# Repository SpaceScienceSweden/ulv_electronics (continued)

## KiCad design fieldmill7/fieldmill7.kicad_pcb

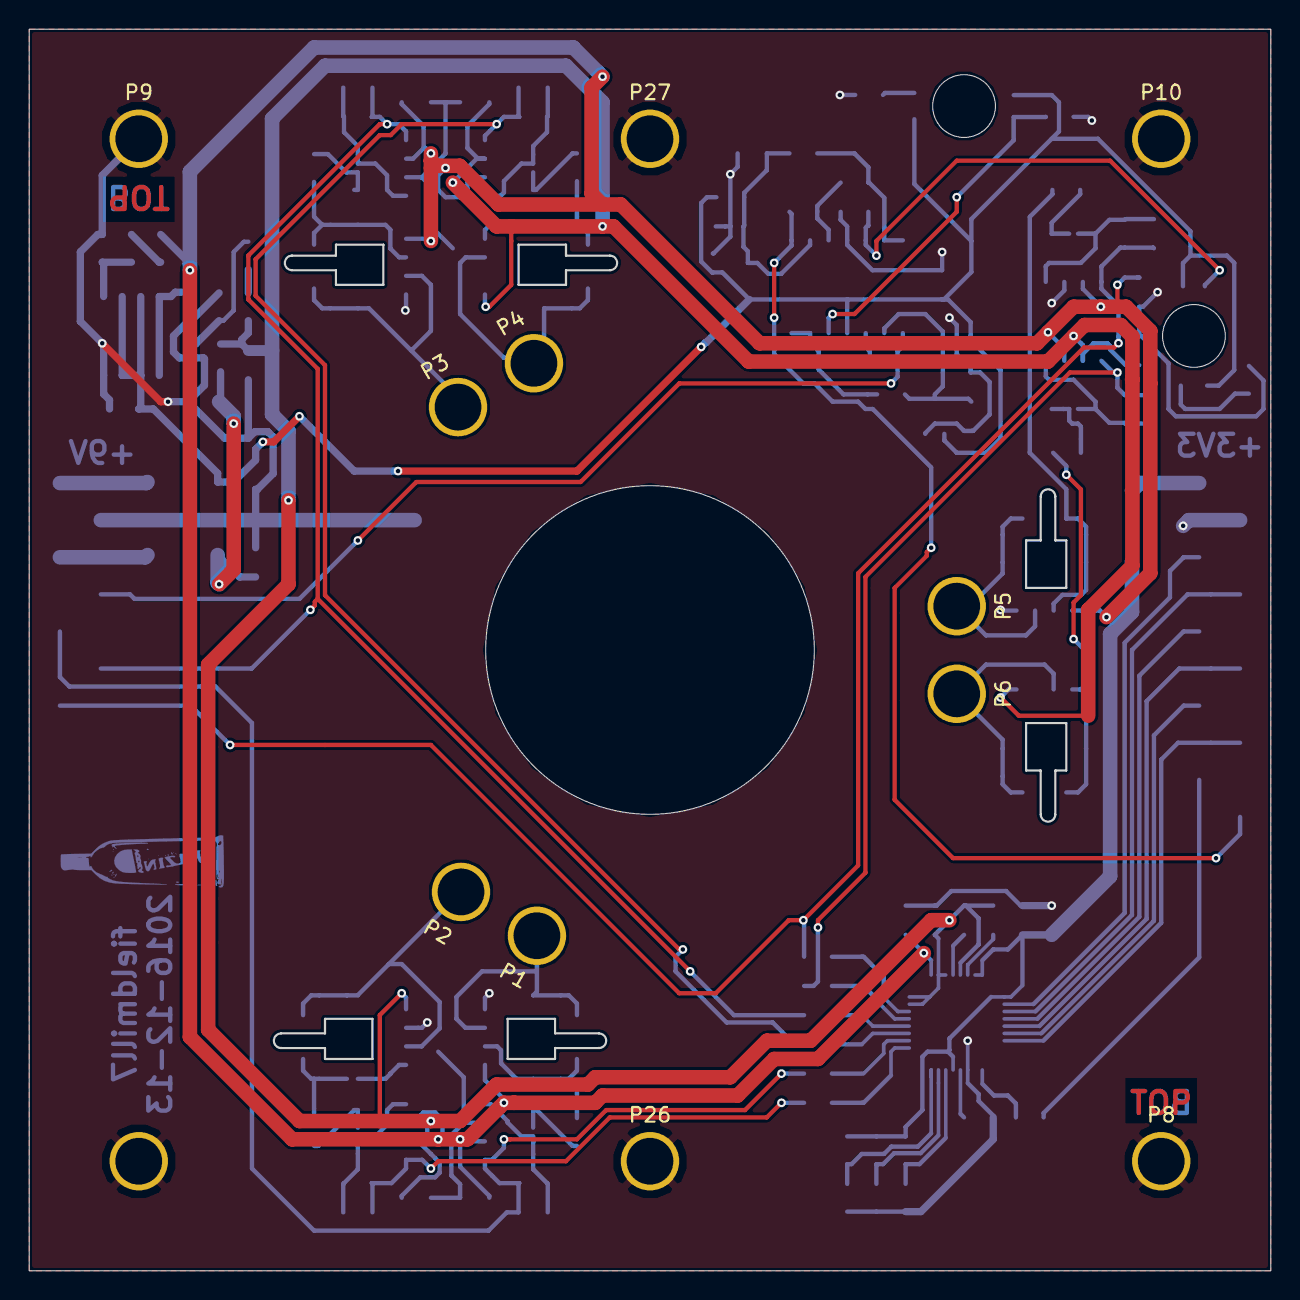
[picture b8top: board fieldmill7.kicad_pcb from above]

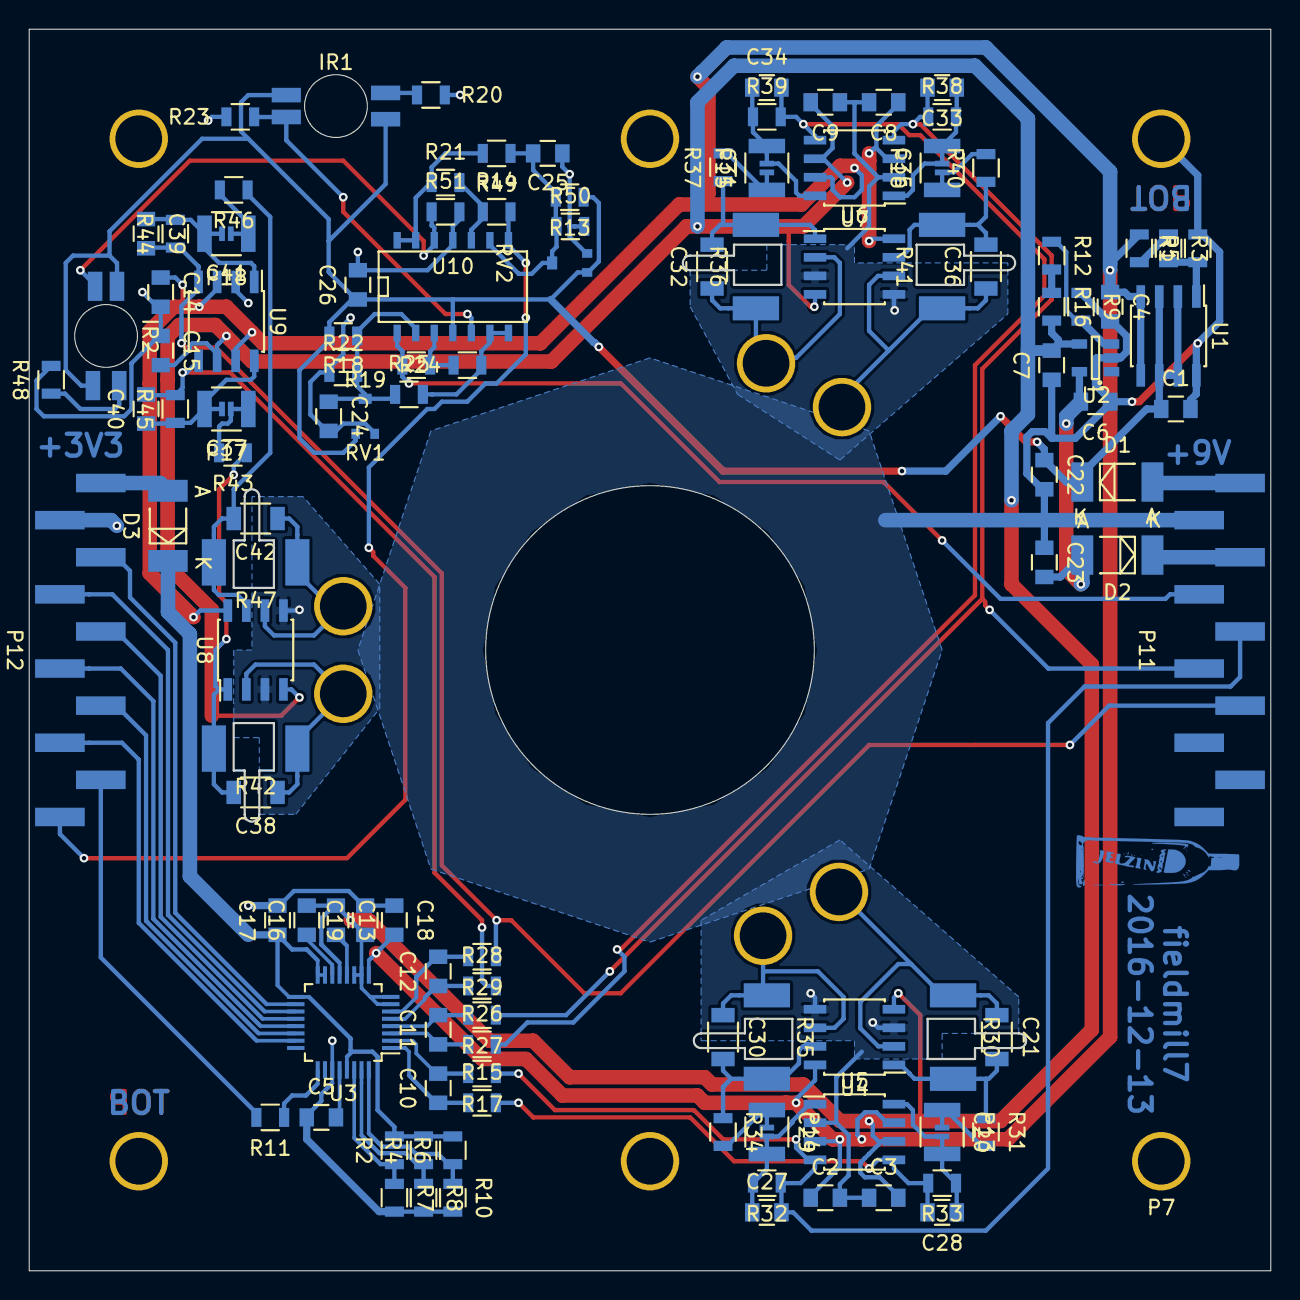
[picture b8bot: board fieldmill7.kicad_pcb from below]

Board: 2 copper layers, 85.0 x 85.0 mm, 130 parts (119 on the bottom side), 75 nets.

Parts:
C1, C2, C3, C6, C8, C9, C14, C15, C24, C25, C26: 100n; C_0805
C4, C7, C22, C23: 10u; C_0805
C5, C13, C16, C17, C18, C19: 1u; C_0805
C10, C11, C12: 10n; C_0805
C20, C29, C31, C35, C37, C41: 220n; C_1210
C21, C30, C32, C36, C38, C42: 10p; C_1206
C27, C28, C33, C34, C39, C40: 1n; C_0805
D1, D2, D3: SMS240; MELF_Standard
IR1, IR2: SG-2BC
P1, P2, P3, P4, P5, P6: SENSOR; M3_PTH
P7, P8, P9, P10, P26, P27: M3; M3_PTH
P11, P12: CONN_01X10; SMD_pinheader_1x10
P13, P14, P15, P16, P17, P18: NO_HIPASS; solder_bridge_1mm
R1, R3, R9, R12, R21, R24: 10k; R_0805
R2, R4, R6, R7, R8, R10: 470; R_0805
R5: 665; R_0805
R11: 50; R_0805
R13, R18: 220k; R_0805
R14, R19, R25, R49: 1M; R_0805
R15, R17, R26, R27, R28, R29: 1k; R_0805
R16: 845; R_0805
R20, R48: 5k6; R_0805
R22, R50: 100k; R_0805
R23, R51: 470k; R_0805
R30, R35, R36, R41, R42, R47: 10M; Resistor_2010_2512_combined
R31, R32, R33, R34, R37, R38, R39, R40, R43, R44, R45, R46: 18k; R_0805
RV1, RV2: 22k; PVZ2A
U1: MAX1659; SOIC-8_3.9x4.9mm_Pitch1.27mm
U2: MIC5270YM5-TR; SOT-23-5
U3: ADS131A04; LQFP-32_5x5mm_Pitch0.5mm
U4, U6, U8: LTC6241; SOIC-8_3.9x4.9mm_Pitch1.27mm
U5, U7, U9: OPA1632; SOIC-8_3.9x4.9mm_Pitch1.27mm
U10: LM324; SOIC-14_N

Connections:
+2V5: C2.1, C4.1, C8.1, C14.1, C18.2, R5.1, U1.4, U1.5, U3.9, U4.8, U5.3, U5.7, U6.8, U7.3, U7.7, U8.8, U9.3, U9.7
+3V3: C17.1, D3.1, R2.2, R4.2, R6.2, U3.15, U3.16, U3.17, U3.29
+9V: C1.1, C22.1, C26.1, D1.1, IR1.A, IR1.C, IR2.A, IR2.C, R13.1, R18.1, RV1.1, RV2.1, U1.2, U1.3, U1.6, U1.7, U10.4
-2V5: C3.2, C7.2, C9.2, C13.1, C15.2, C16.2, C19.1, R16.2, U2.4, U3.7, U3.8, U3.10, U3.11, U3.13, U4.4, U5.6, U6.4, U7.6, U8.4, U9.6
-9VA: C6.2, C23.2, D2.2, U2.5
//CS: P12.3, U3.23
//DONE: P12.8, U3.18
//DRDY: P12.7, U3.19
/ITACH: P11.4, R19.2, U10.1
/MISO: P12.5, U3.21
/MOSI: P12.6, U3.20
/QTACH: P12.1, R14.2, U10.8
/SCLK: P12.4, U3.22
/channel1/OUT+: C27.2, P11.5, R17.1, R32.1, U5.4
/channel1/OUT-: C28.2, R15.2, R33.2, U5.5
/channel1/SENSORN: C21.1, P2.1, R30.1, U4.2
/channel1/SENSORP: C30.1, P1.1, R35.1, U4.6
/channel2/OUT+: C33.2, P11.6, R27.1, R38.1, U7.4
/channel2/OUT-: C34.2, R26.2, R39.2, U7.5
/channel2/SENSORN: C32.1, P4.1, R36.1, U6.2
/channel2/SENSORP: C36.1, P3.1, R41.1, U6.6
/channel3/OUT+: C39.2, P11.7, R29.1, R44.1, U9.4
/channel3/OUT-: C40.2, R28.2, R45.2, U9.5
/channel3/SENSORN: C38.1, P6.1, R42.1, U8.2
/channel3/SENSORP: C42.1, P5.1, R47.1, U8.6
/f_ADC: P12.2, R11.2
GND: C1.2, C2.2, C3.1, C4.2, C5.1, C6.1, C7.1, C8.2, C9.1, C14.2, C15.1, C17.2, C18.1, C19.2, C22.2, C23.1, C24.2, C25.2, C26.2, P7.1, P8.1, P9.1, P10.1, P11.2, P12.9, P26.1, P27.1, R1.2, R7.2, R8.2, R9.1, R10.2, R20.2, R22.2, R23.2, R48.2, R50.2, R51.2, RV1.3, RV2.3, U1.8, U2.2, U3.27, U4.3, U4.5, U5.2, U6.3, U6.5, U7.2, U8.3, U8.5, U9.2, U10.11
unnamed: C5.2, U3.28
unnamed: C10.1, R15.1, U3.1
unnamed: C10.2, R17.2, U3.2
unnamed: C11.1, R26.1, U3.3
unnamed: C11.2, R27.2, U3.4
unnamed: C12.1, R28.1, U3.5
unnamed: C12.2, R29.2, U3.6
unnamed: C13.2, U3.12
unnamed: C16.1, U3.14
unnamed: C20.1, P13.2, R31.2
unnamed: C20.2, C28.1, P13.1, R33.1, U5.8
unnamed: C21.2, R30.2, R31.1, U4.1
unnamed: C24.1, R18.2, R22.1, R25.1, RV1.2, U10.2
unnamed: C25.1, R13.2, R49.1, R50.1, RV2.2, U10.9
unnamed: C27.1, C29.2, P14.1, R32.2, U5.1
unnamed: C29.1, P14.2, R34.2
unnamed: C30.2, R34.1, R35.2, U4.7
unnamed: C31.1, P15.2, R37.2
unnamed: C31.2, C34.1, P15.1, R39.1, U7.8
unnamed: C32.2, R36.2, R37.1, U6.1
unnamed: C33.1, C35.2, P16.1, R38.2, U7.1
unnamed: C35.1, P16.2, R40.2
unnamed: C36.2, R40.1, R41.2, U6.7
unnamed: C37.1, P17.2, R43.2
unnamed: C37.2, C40.1, P17.1, R45.1, U9.8
unnamed: C38.2, R42.2, R43.1, U8.1
unnamed: C39.1, C41.2, P18.1, R44.2, U9.1
unnamed: C41.1, P18.2, R46.2
unnamed: C42.2, R46.1, R47.2, U8.7
unnamed: D1.2, P11.1
unnamed: D2.1, P11.3
unnamed: D3.2, P12.10
unnamed: IR1.E, R23.1, U10.5
unnamed: IR1.K, R20.1
unnamed: IR2.E, R51.1, U10.12
unnamed: IR2.K, R48.1
unnamed: R1.1, R3.2, U1.1
unnamed: R2.1, R7.1, U3.30
unnamed: R3.1, R5.2
unnamed: R4.1, R8.1, U3.31
unnamed: R6.1, R10.1, U3.32
unnamed: R11.1, U3.25
unnamed: R9.2, R12.1, U2.3
unnamed: R12.2, R16.1
unnamed: R14.1, R21.2, U10.10
unnamed: R19.1, R24.2, U10.3
unnamed: R21.1, R49.2, U10.13, U10.14
unnamed: R24.1, R25.2, U10.6, U10.7

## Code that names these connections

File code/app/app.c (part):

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#define WDR_IN_RECVLINE 1

/* RS-485 needs a DE pin */
#define RS485_DE_PORT PORTD
#define RS485_DE_DDR  DDRD
#define RS485_DE_BIT  (1<<5)

#define ONEWIRE_PORT  PORTG
#define ONEWIRE_PIN   PING
#define ONEWIRE_DDR   DDRG
#define ONEWIRE_MASK  (1<<4)

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
//called by setup_xmem() in .init3 (init3.c), before main()
void clear_xmem (void) {
  //assert /EN_XMEM (PG3)
  DDRG |= (1<<3);
  PORTG &= ~(1<<3);

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  UBRR1H = UBRR / 256;

  //TX and DE
  DDRD |= (1<<PD3);
  //ensure we're in RX mode
  RS485_DE_DDR |= RS485_DE_BIT;
  RS485_DE_PORT &= ~RS485_DE_BIT;
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

static void setup_timers() {
  //PB5 = OC1A, PB6 = OC1B, PB7 = OC1C. inverted drive signals
  //pwm frequency range is 500 Hz .. 20 kHz
  //WGM=3 -> TOP=0x3FF -> (14745600/1024) = 14400 Hz (10-bit fast PWM)
  uint8_t wgm = TIMER1_WGM;
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  //set MOSI and SCK as output, obviously
  //but also set /SS as output or a low input will put us in SPI slave mode
  //incidentally this also asserts EN_APWR
  //enable pull-up on MISO (PB3) too, ADS131A04 requires it
  PORTB |= (1<<0) | (1<<3);
  DDRB |= (1<<0) | (1<<1) | (1<<2);

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#endif

static inline void adc_deselect(void) {
  //PF0..4 = ADC (must be zero)
  //PF5..7 = /CS_ADCn
  PORTF = 7<<5;
}

static inline void adc_select(uint8_t id) {
  //assert relevant /CS pin
  PORTF = (7<<5) & ~(1<<(PF5+id));

  //t_d(CSSC) = 16 ns, each instruction takes 135 ns
  //hence no need to delay further after asserting /CS
}

static void setup_adc_pins() {
  //PF5..7 = /CS_ADC0..2
  DDRF |= (1<<5) | (1<<6) | (1<<7);
  adc_deselect();

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}

void set_74153(uint8_t ch) {
  DDRD |= (1<<PD6) | (1<<PD7);
  PORTD = (PORTD & ~((1<<PD6) | (1<<PD7))) | (ch << PD6);
}

//must be called with an id of an ADC which is active
static uint8_t get_tach_pin(uint8_t id) {
  set_74153(id);
  return PIND & (1<<PD4);
}

#if FEATURE_SAMPLES == 1
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      start_section("INFO");
      printf_P(PSTR("ADC %hhu: ADC_ENA=%hhx\r\n"), id, ena);

      portf &= ~(1<<(PF5+id));
      if (pc == 0) {
        lastena = ena;
        pc = popcount(ena);
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  for (uint8_t x = 0; x < romcnt; x++) {
    temps[x].rom12[0] = roms[x*8+1];
    temps[x].rom12[1] = roms[x*8+2];
    ds18b20read( &ONEWIRE_PORT, &ONEWIRE_DDR, &ONEWIRE_PIN, ONEWIRE_MASK, &roms[x*8], &temps[x].temp );
  }
}

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        if (c == '!') {
          //search for ROMs again
          romcnt = 0;
          ds18b20search( &ONEWIRE_PORT, &ONEWIRE_DDR, &ONEWIRE_PIN, ONEWIRE_MASK, &romcnt, roms, sizeof(roms) );
          if (romcnt > 6) romcnt = 6; //just to be sure
        }
        start_section("ONEWIRE");
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        printf_P(PSTR("Starting temperature conversion...\r\n"));

        //tell all devices to do a temperature conversion
        ds18b20convert( &ONEWIRE_PORT, &ONEWIRE_DDR, &ONEWIRE_PIN, ONEWIRE_MASK, NULL );

        //issue read slots, wait for all devices to transmit 1
        while (!onewireReadBit( &ONEWIRE_PORT, &ONEWIRE_DDR, &ONEWIRE_PIN, ONEWIRE_MASK )) {
          wdt_reset();
        }

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          }
        }
      escapeit:
        //leave with VGND=0
        set_vgnds(512);
#endif // FEATURE_TWIDDLE_VGND
#if FEATURE_PROGRAMS == 1
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  DDRB |= (1<<0);
  PORTB &= ~(1<<0);

  //CPU utilization on PF6
  //FIXME: this is the same as /CS_ADC1
  //       we don't have any LED installed, so we could use a different pin for CPU
  //       PD0 or PD1 may be suitable
  DDRF |= (1<<6);
  CPU_USAGE_OFF();

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  sei();

  //search for 1-wire devices
  ds18b20search( &ONEWIRE_PORT, &ONEWIRE_DDR, &ONEWIRE_PIN, ONEWIRE_MASK, &romcnt, roms, sizeof(roms) );
  if (romcnt > 6) romcnt = 6; //just to be sure

  set_vgnd(0, vgnds[0]);
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        //maybe we have some data? :>
        if (temp_conversion_in_progress) {
          //every device transmitting 1?
          if (onewireReadBit( &ONEWIRE_PORT, &ONEWIRE_DDR, &ONEWIRE_PIN, ONEWIRE_MASK )) {
            //hooray!
            header.num_temps = romcnt;
            read_temps(temps);
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
        if (!temp_conversion_in_progress) {
          //tell all devices to do a temperature conversion
          ds18b20convert( &ONEWIRE_PORT, &ONEWIRE_DDR, &ONEWIRE_PIN, ONEWIRE_MASK, NULL );
          temp_conversion_in_progress = 1;
        }

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
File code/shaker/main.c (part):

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char hello[4000];

static void setup_xmem() {
  //assert /EN_XMEM (PG3)
  DDRG |= (1<<3);
  PORTG &= ~(1<<3);

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  UBRR0L = UBRR;
  UBRR0H = UBRR / 256;

  DDRE |= (1<<PE1);
}

static void setup_uart1() {
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  UBRR1H = UBRR / 256;

  //TX and DE
  DDRD |= (1<<PD3) | (1<<PD5);
}

static unsigned freeRam () {
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
  //assert relevant /CS pin
  if (id == 0) {
    PORTD &= ~(1 << PD0);
  } else if (id == 1) {
    PORTD &= ~(1 << PD1);
  } else {
    PORTF &= ~(1<<7);
  }
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

static void setup_adc_pins() {
  //CS pins = PD0, PD1, PF7
  PORTD |= (1<<0) | (1<<1);
  PORTF |= (1<<7);
  DDRD |= (1<<0) | (1<<1);
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
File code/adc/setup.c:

#include "main.h"

static void cls() {
  //clear screen. maybe there's a better way?
  int y;
  for (y = 0; y < 100; y++) {
    printf_P(PSTR("\033[%i;0H"), y);
    printf_P(PSTR("                                                                      "));
  }
}

static void setup_sintab() {
  int x;
  for (x = 0; x < 256; x++) {
    //this approximation minimizes harmonic distortion when limited to 8 bits
    //see optimize_sintab.m
    sintab[x] = 124.72 * sin(2*M_PI*x/256);
  }
}

void disable_tachs() {
  EIMSK &= ~((1<<4) | (1<<5));
  
  //clear associated interrupt flags
  EIFR |= (1<<4) | (1<<5);
}

//sets up tachometer interrupts (INT4, INT5)
void setup_tach(uint8_t id) {
  //enable INT4 and INT5
  EIMSK |= (1<<(4+id));
  //rising edge
  EICRB |= (3<<ISC40) | (3<<ISC50);
}

static void setup_uart0() {
  //double speed for higher UBRR resolution
  UCSR0A |= (1<<U2X);
  //enable RX and TX
  UCSR0B = (1<<RXEN) | (1<<TXEN);
  //8 data bits, 2 stop bits
  UCSR0C = (1<<USBS) | (3<<UCSZ00);
  UBRR0L = UBRR;
  UBRR0H = UBRR / 256;
  
  DDRE |= (1<<PE1);
}

static void setup_uart1() {
  //double speed for higher UBRR resolution
  UCSR1A |= (1<<U2X);
  //enable RX and TX
  UCSR1B = (1<<RXEN) | (1<<TXEN);
  //8 data bits, 2 stop bits
  UCSR1C = (1<<USBS) | (3<<UCSZ10);
  UBRR1L = UBRR;
  UBRR1H = UBRR / 256;
  
  DDRD |= (1<<PD3);
}

void disable_timer3() {
  ETIMSK &= ((1<<TOIE3) | (1<<OCIE3A));
}

void setup_timer3() {
  //normal port operation, normal counter mode
  TCCR3A = 0;
  //no noise canceller, no input capture, normal mode, prescaler=1
  TCCR3B = 1;

  //trigger TIMER3_COMPA_vect in the middle of the range
  OCR3A = 0x8000;

  //pre-emptively clear TOV1
  TCNT3 = 0;
  ETIFR |= ~(1<<TOV3);

  //enable Timer3 overflow and COMPA match interrupts
  ETIMSK |= (1<<TOIE3) | (1<<OCIE3A);
}

static void setup_motor_pwm() {
  //PB5 = OC1A, PB5 = OC1B. inverted drive signals
  //pwm frequency range is 500 Hz .. 20 kHz
  //WGM=1 -> TOP=0xFF -> (7372800/256/2) = 14400 Hz (8-bit phase-correct PWM)
  uint8_t wgm = 1;
  TCCR1A = (3<<COM1A0) | (3<<COM1B0) | (3<<COM1C0) | ((wgm&3) << WGM10);
  //enable clock, no prescaler
  TCCR1B = (((wgm>>2)&3) << WGM12) | (1<<CS10);
  TCCR1C = 0;

  //0% duty to start
  OCR1A = 0;
  OCR1B = 0;
  OCR1C = 0;

  //enable outputs
  DDRB |= (1<<5) | (1<<6) | (1<<7);
}

//http://stackoverflow.com/questions/960389/how-can-i-visualise-the-memory-sram-usage-of-an-avr-program
static int freeRam () {
  extern int __heap_start, *__brkval; 
  int v; 
  return (int) &v - (__brkval == 0 ? (int) &__heap_start : (int) __brkval); 
}

void setup() {
  //setup stdout for printf()
  stdout = &mystdout;

  setup_motor_pwm();

  setup_uart0();
  setup_uart1();
  disable_tachs();

  if (1) {
    //put RS-485 bus in TX mode (not yet connected)
    //this could also be done in the UDRE ISR
    DDRF |= 2;
    PORTF |= 2;
  }

  printf_P(PSTR("%i B SRAM free\r\n"), freeRam());
  memset((void*)adc_state, 0, sizeof(adc_state));
  setup_adc_pins();
  disable_adc(0);
  disable_adc(1);
  config_adc(0);
  config_adc(1);

  //CPU usage monitor on PF2
  DDRF |= 1 << 2;

  //ISP disabler on PF3
  //turns out this isn't really needed, since the 4016 on the ISP signals
  //is enough to provide decent termination
  //still probably a good idea to keep around
  DDRF  |=   1<<3;
  PORTF &= ~(1<<3);

  setup_sintab();
}

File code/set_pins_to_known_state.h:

  //put pins in known state
  //input + pull-up unless otherwise noted
  DDRA = 0b00000000;  PORTA = 0b11111111; // XMEM AD0..7
  DDRB = 0b11110001;  PORTB = 0b11111110; // EN_APWR = 0 (off), /SD_CS = 1 (off), PWM0..2 = 1 (off)
  DDRC = 0b00000000;  PORTC = 0b11111111; // XMEM A8..15
  DDRD = 0b00100000;  PORTD = 0b11011111; // RS485_DE = 0
  DDRE = 0b00011100;  PORTE = 0b11011111; // /CS_VGND0..2 = 1
  DDRF = 0b11100000;  PORTF = 0b11100000; // /CS_ADC0..2 = 1, no pull-ups on ADC0..4
  DDRG = 0b00001111;  PORTG = 0b11111011; // ALE = 0, /EN_XMEM = 1, /RD = 1, /WR = 1

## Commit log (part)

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2018-04-05 Make deeper blind vias 0.7 mm, clean up
2018-04-05 Reroute ch2 guard
2018-04-06 Do the same thing with ch3
2018-04-06 Extend some blind vias from In3 down to In4 and/or B
2018-04-06 Merge blind vias
    python3 merge_blind_vias.py fieldmill10.kicad_pcb > temp.sed && \
    sed -i -f temp.sed fieldmill10.kicad_pcb
2018-04-06 Via fence inside ch3
2018-04-06 Last one \o/
2018-04-07 Move silk labels under cans to on top of solder mask
2018-04-16 Add mechanical drawing of female header
2018-04-16 Update LPPB122 footprints on cpu3 and credits
2018-04-18 fm10: Add fit_field for KiBoM
2018-04-20 More BOM stuff
2018-04-23 Restrict Z drill to below In2.Cu
    This way we can have vias down to In2.Cu to connect either side of the SMD headers
2018-04-24 Make virtual parts smd, let BOM/PnP filter take care of this
2018-04-24 CSV fab BOM
2018-04-24 Route horizontals @ headers, thicken some power traces
2018-04-24 Everything connected
2018-04-25 Same thing for In2.Cu-B.Cu
2018-04-25 Get 3D model into LPPB122NFSP
2018-04-25 Design rules for new stackup
2018-04-26 Seems to work fine
2018-04-26 Ground vias will need to go do In3.Cu by stacked microvias
2018-04-26 Clean up In1.Cu
2018-04-26 Connect to VGND driver, multiple staggered microvias
2018-04-26 Reconnect guard fences inside cans
2018-04-26 Stagger feeds to ops
2018-04-26 Missed some
2018-04-26 More stitching
2018-04-26 Smaller thermals on exposed copper areas
2018-04-26 Clean up in In3 and In4
2018-04-26 Stich In1-In2
    Some finger slips -> vias instead of inner vias. Fixing that soon
2018-04-27 Fix B.SilkS
2018-04-27 Pour most of In4.Cu
    Better copper balance
2018-04-27 Update fm10 TODOs
2018-05-02 Fyrdubbla vior på signalgenomföringar
2018-05-02 Thicken som traces to 0.3 mm
2018-05-02 Some more
2018-05-02 Shorten SCLK
2018-05-02 Make In4.Cu pour a bit better, add missing GND in bottom right
2018-05-03 Double up on some more microvias
2018-05-03 Enlarge VGND fills on In4.Cu
2018-05-03 Conform pcb module attributes (virtual vs insert) to BOM
    Also newly generated BOMs
2018-05-04 Try to organize things in revisions
2018-05-04 Switch to LTC6241HS8#TRPBF
    All parts should now tolerate up to +125°C
2018-05-04 Darn MAX504
2018-05-04 NCAB suggested stackup
2018-05-04 Avoid space in IR2 component value
2018-05-04 Don't forget silver plating
2018-05-07 cp cpu3 cpu4
2018-05-07 Add to footprint
2018-05-07 cpu4: Use the 3x12 variant
2018-05-07 cpu4: rm U8
2018-05-08 cpu4: Switch D2 and D8 to same SMA diode used in fm10
2018-05-08 Add 3D for THN 30-2415(WI)
2018-05-09 fm10: Add fiducials
2018-05-14 cpu4: Update TODOs
2018-05-14 cpu4: Remove C9, C10, C36, change C34 to 100n
    There's more than enough bulk capacitance
2018-05-17 fm10-rev4: Fix BOM having extra sheets, derp
    Regenerate gerbers while we're at it, with updated date in bottom copper
2018-05-17 cpu4: Simplify
    Removed all unused configuration resistors
    Removed 100 nF caps on optional clock buffers
    EXTRA1..4 is no more
    Connected PD0..1 to TACH0..1
    Tied all EN_VGND together
    Made PF5..7 only do /CS_ADC0..2
2018-05-17 cpu4: Lock graphics
2018-05-18 fm10: Fix STTH102A Elfa PN
2018-05-18 rm the older revisions
    rev4 is what was sent to the fab
    rev5 is what is actually being produced
2018-05-18 cpu4: Fit everything on the board
    Next up, try to move everything from the bottom side to the top
2018-05-21 cpu4: Nix ATmegaS128
2018-05-21 cpu4: Move silks around, don't fit µSD by default
2018-05-21 cpu4: Start routing
2018-05-22 cpu4: Use 0.25 mm traces
    0.3 mm caused DRC issues somehow
2018-05-23 cpu4: Routed everything
    Might still tweak some things, like copper pour
2018-05-23 Add 3D model for TMR 6-2421WI, add it to the footprint
    Footprint is still called RSO-2412D which is a bit ugly but eh
2018-05-23 Add 3D model for TSR 1
2018-05-29 Square demodulator
2018-05-29 Optimize
2018-05-29 Finish implementing square_demod_analog()
2018-06-01 Clear ICn early, poll PE7 in square_demod_analog()
    At maximum sample rate we're cutting it quite close.
    /DRDY is high only for 1.2 µs with one ADC active @ 38.4 kHz,
    meaning roughly 16 cycles to check stat1_data, dec+check num_frames_left and start polling PE7.
    Replacing the SPIF loops in read_samples_fast() with hard-coded NOPs might now be appropriate..
2018-06-08 Add support for 16-bit samples
    Kind of messy, but seems to work fine
2018-06-08 More elaborate reset
    This feels very flaky
2018-06-08 Add another throughput measurement
    We probably can't do much about the cycles being wasted between bytes withouth getting into asm territory
2018-06-15 fm10: Do not fit R8 -> 16-bit samples
2018-06-15 mv rev5 -> rev4.1
2018-06-15 cpu4: Push some tracks around, repour
2018-06-15 cpu4: BOM 10u50V
2018-06-15 cpu4: BOM 22p
2018-06-15 cpu4: BOM diodes and polyfuse
2018-06-29 cpu4: Make top copper pour more connected
2018-07-02 cpu4: Fix ERC
2018-07-02 cpu4: BOM inductors, use L_1008 footprint, update PCB
2018-07-02 cpu4: BOM IRLL024NPBF, un-BOM screw holes
2018-07-02 cpu4: BOM 71V124SA12YGI
2018-07-02 cpu4: BOM DS18B20Z+ (replaces DS18B20Z)
2018-07-02 cpu4: BOM SN74AHC573DW
2018-07-02 cpu4: BOM TMR 6-2421WI
2018-07-02 cpu4: We also need to check what make of crystal we're using
2018-07-02 cpu4: Do inventory on expensive parts
2018-07-02 cpu4: BOM crystal
    Made sure to use industrial grade rather than the current Auris part.
2018-07-02 cpu4: Replace MAX3485CSA+ with MAX3483ESA+, the industrial variant
2018-07-11 cp RSO-2412D_v2.kicad_mod TMR_6-2421WI.kicad_mod
    Else we get RSO* in the BOM which is probably confusing
2018-07-16 Update TODOs, fiddle with silk, fit_field 'lab' should be '+lab'
2018-07-16 Done with the PCB it seems
2018-07-16 Fixed a minor blemish
2018-07-16 BOM, 1% resistors
2018-08-10 cpu4-1.1: New top copper, add fiducials to paste and PnP
2018-08-30 145 B max typical IQ packet size
2018-09-13 Add STAT_* to FMIQ
2018-09-13 Turn off echo in setbaud target
2018-09-13 Add some #defines to turn on/off some features
2018-09-13 Wire version 3, more stats
    We have min, max, mean and mean absolute value.
2018-09-14 Change IQ computation, keeping result in int16_t range
    If we have 128k RAM we can cram 65535x 16-bit samples in there and still be in range.
2018-09-23 Add reel specs
    They're in Swedish, sorry
2018-10-11 Account for 3 vanes in demodulation
    This makes mean_abs very close to abs(iq), as expected
2018-10-20 Update manual, separate bootloader target in Makefile
2018-10-31 manual: Fix pin assignment, add fm10 voltage ranges
2018-10-31 Print details of ROM, fixed RAM and stack use
2018-11-07 Switch to WGM 14, Fast PWM
    This gives TIMER1_OVF at the same rate as WGM 7 with prescaler 8,
    but higher TCNT1 accuracy.
2018-11-07 Add FatFs AVR sample
    All unnecessary files removed, no changes yet.
2018-11-08 Disable some FAT/MMC features we don't need for now
    Saves on having to wait for another 32k of Flash to transfer
2018-11-09 Remove garbage, don't unroll accumulate_square_interval() for now
    Waiting on flashing is very tiring
2018-11-15 Fix another fm_map[] bug
2018-11-15 Manual changes for fm10
    Having to replace R56 is annoying, but not a showstopper.
2018-11-19 Optimize even more
2018-11-20 Fully tested optimized capture, 38.4 kHz
    Previous commit relied on SPDR double-buffering, which isn't a thing.
    There is also a need to wait a few extra cycles here and there due to ADS131A04 peculiarities.
    It worked in the end though (yay!)
2018-11-21 Read STAT_1PNS before capture(), print STAT_PN
    This fixes some issue when using more than one FM.
    It might just be that the new FM is a bit picky.
    Either way, we're only interested in errors during capture().
2018-11-22 Copy avr51.xn linker script so we can modify it
2018-11-28 Update fm10 part of manual
2018-11-30 Frama-C-ify capture()
    We'll be able to prove parts of the code correct this way
2018-11-30 Move and prove compute_min_max()
2018-12-06 Set cb.num_frames and OCR1n[1..2] correctly
2018-12-18 Update cpu4 and fieldmill10 with new 3d models
2019-01-10 Getting there, but this will probably be slow
2019-01-15 Moving the test runs elsewhere
2019-01-15 Ignore *.O
2019-01-15 Add complete cpu4-1.1 instructions
    These should just be cpu4-1.0 with cpu4-1.1 copied on top
2019-01-16 Refactor capture_and_demod(), use tach mean as trigger level, output ratio between longest and shortest tach period
2019-01-16 Move some FEATURES to separate files
2019-01-21 Fix bug that caused weekend test to have no calibration (gah!)
2019-02-12 Mess around with credits
2019-02-14 Quarter speed for 2019-02-14 14:25 test
2019-02-15 Add temperatures, voltages and markers to capture_block_s
    Plus some other minor changes like allowing more than 255 entries̈́
2019-02-20 feature_blocks: Fix reading temps, print temps and volts
2019-02-20 Add some more rect fitting methods
    Turns out the one we started with is best
2019-03-04 Add settings.mk, make app/ Makefile usable on its own
2019-03-13 Add forgotten version = 3
2019-03-13 Fix PE5 state in bootloader too
2019-04-15 Make bootstrap_tach_mean_assert_mean_ok easier to prove
2019-04-15 Implement the rest of accumulate_square_interval
2019-04-16 Clean up accumulate_*()
    Number of goals reduced from around 130 to 99
2019-04-16 Call it 'verify' instead of 'prove'
2019-04-17 Use verified accumulate_square_interval_2(), add performance results
    The verified one is ~3% slower, which is acceptable for the guarantees given
2019-04-17 Finally got accumulate_square_interval_2() to verify properly
2019-04-18 Forgot to compute NQ, compute nsum* instead
    For some reason WP isn't able to prove the behavior of NQ,
    and having an array for nsum* didn't work either.
2019-04-18 Add verified find_tachs()
2019-04-21 Verify capture_and_demod()
    This took quite a bit of hacking the other verified routines
2019-04-23 Don't create verify file
2019-04-24 Optimize compute_min_max()
    61 ms -> 30 ms
2019-04-24 Put edge_pos[] in known position
    This speeds up find_tachs() slightly: 7 ms -> 6 ms
2019-04-24 Optimize accumulate_quadrant()
    demod_tachs(): 39 ms -> 36 ms
2019-04-25 Move Q1..4 and NQ to .bss
    This reduces stack usage more than it increases .bbs, saving RAM.
    Verified.
2019-04-25 Dump .data and .text
2019-04-25 Recompute max_frames etc every round
    This needs to be done for the same RPM to be printed and other things
2019-04-27 Verify parse64() and print64()
2019-05-15 Add CodeLite project
2019-06-20 Add CD4504B
2019-06-24 Add LIS3MDL
2020-01-02 Make capture() verify using Frama-C 20.0 (Calcium)
2020-01-03 Verify popcount()
2020-01-03 Verify set_vgnds()
2020-01-04 Verify init_cb_cbc()
    memcpy() doesn't work for some reason, SET_MARKER replaces it.
2020-01-04 Rearrange things
2020-01-05 Verify popcount, SPI communication stuff
2020-01-07 WIP scripts
2020-01-07 Switch to rreg_not_ena()
2020-01-07 Add and use machine files for gcc_avr_16
    Partial file for gcc_avr_8
2020-01-08 Re-prove accumulate_square_interval_2(), downsize psize and paccu to 24-bit
    We've proved 16 bit is enough
2020-01-08 Improve bootstrap_tach_mean() proof
2020-01-10 Fix build
    app.c has lots of code which is yet to be verified
2020-01-11 Split out and re-prove parts of capture_and_demod()
2020-01-11 Stricter memory model, force using native integer types
2020-01-12 Rename scripts
2020-01-12 Change definition of valid_adc_configuration_part2() to something more sensible, prove more things
    accumulate_square_interval_2() needs some attention.
    set_block_motor_speed() now deals with wreg() failing.
2020-01-12 Adjust some proofs so everything verifies without the cache
2020-01-14 Make use of setup_inner() and popcount4() in square_demod_analog()
2020-01-14 Yet better typed_nocast_accumulate_square_interval_2_ensures proof using contraposition
2020-01-15 Remove unused proof script
2020-01-24 Use ghost function to prove clk12 assertions
    Much more elegant and faster proof compared to trying hundreds of values
2020-01-24 Simplify remaining 'try all numbers up to 255' proofs
2020-01-28 rreg_ena(): Better emulation of ID_MSB/ID_LSB, and some related stuff
2020-01-28 Bring back a script that was actually fine
2020-01-28 Adjust wreg_checked() according to changes in rreg_ena()
2020-01-29 Fix Frama-C warning about 2.56
2020-01-29 Re-run TIP
2020-02-07 Verify writeEEpromPage() and readFlashPage()
2020-02-07 Verify send_string_internal()
